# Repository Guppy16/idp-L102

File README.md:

# IDP L102
Team Name: Root g \
Robots: pi, e

The ultimate repo for the idp

## Task
Design and simulate 2 similar robots with the same controller to collect coloured blocks in an arena.

## Assumptions

Sensor Modules:
- Colour sensor: 1 pixel camera; range of 1 - 10 cm
- Ultrasound sensor: Distance sensor; range = 20 - 140 cm; 3 cm resolution; 5% std
- IR sensor: Same as ultrasound
- Position sensor: GPS sensor; 1 cm accuracy; 3cm resolution
- Rotation sensor: Compass sensor; 5cm resolution

---
## Quick Links
- [Webots Tutorials](https://cyberbotics.com/doc/guide/tutorials)
- [Parts list](https://www.vle.cam.ac.uk/pluginfile.php/19716321/mod_resource/content/0/Tools%20and%20Parts%20List%20Rev%202.0.pdf)
- [CAD Model](https://drive.google.com/drive/folders/1H2YYnImyA4o20oNFYkEqHbo80u9imQ9U?usp=sharing)
- [G Drive Folder](https://drive.google.com/drive/folders/1ipIikCvn5a5h6eHkmM2m4k-qFC2ZiWPo)

---
## Schedule
- Week 1
  - Tue 26 14:30 - [First Presentation](https://docs.google.com/presentation/d/1Jz8pw5dtujUt2GG7nFzDspJj2hsbr5QpLF5pbWbA2lo)
- Week 2
  - Thurs 28 16:00 - [First Report](https://docs.google.com/presentation/d/1Jz8pw5dtujUt2GG7nFzDspJj2hsbr5QpLF5pbWbA2lo)
  - Tue 2 14:30 - [Progress Meeting 1](https://docs.google.com/presentation/d/1rXteifI9VppYjKGW0S_Uu-YhoCQ_Fu2L5HWq04Rq7eM)
- Week 3
  - Tue 9 14:30 - [Progress Meeting 2](https://docs.google.com/presentation/d/10YraGNGObi2IVQ-5OzObUJLeiZdhKT9rYpSfk6eRZUg)
- Week 4
  - Thurs 11 09:00 - First Competition
  - Tue 16 09:00 - [Final Presentation](https://docs.google.com/presentation/d/1EIgQiFh6fY0tn3hVZZiFkF7x_DoJgEBwd8sGT5k-Sp4)
  - Wed 17 14:00 - Final Competition
- Week 5
  - Mon 22 16:00 - Final Report and Documentation Deadline

## Plan
- [Gannt Chart](https://docs.google.com/spreadsheets/d/1-Yt5QpvAf2re6IKUbvELp7eMGsR5QatMflTM9JjYLDc)

- Before the first Presenetation ~ 5 days
  - [x] Gannt chart -> [ ] Make this better
  - [x] Get used to Webots ~ 2 days
  - [x] Initial CAD and PCB design ~ 5
  - [x] Inital algorithms for navigation ~ 4
- Before progress Meeting 1 ~ 7 days
  - [x] Complete simulation of environment (2 robots)
  - [x] Complete cad design of bulk components ~ 5
  - [x] Finished full schematic ~ 3
  - [x] Started implementing algorithms ~ 3
- Before Progress Meeting 2 ~ 7 days
  - [x] Finished CAD design
  - [x] Implemented Algorithms
  - [x] Start documentation
- Before First Competition ~ 2 days
  - [x] Fully tested algorithms in simulation
- Before Final Presentation
  - [x] Complete presentation ~ 
- Before Final Competition
  - [x] Improved the simulation environment
  - [x] Improved algorithms
- Before Final Report
  - [x] Mechanics Docs
  - [x] Electrical Docs
  - [x] Software Docs
  - [x] Cleanup README file

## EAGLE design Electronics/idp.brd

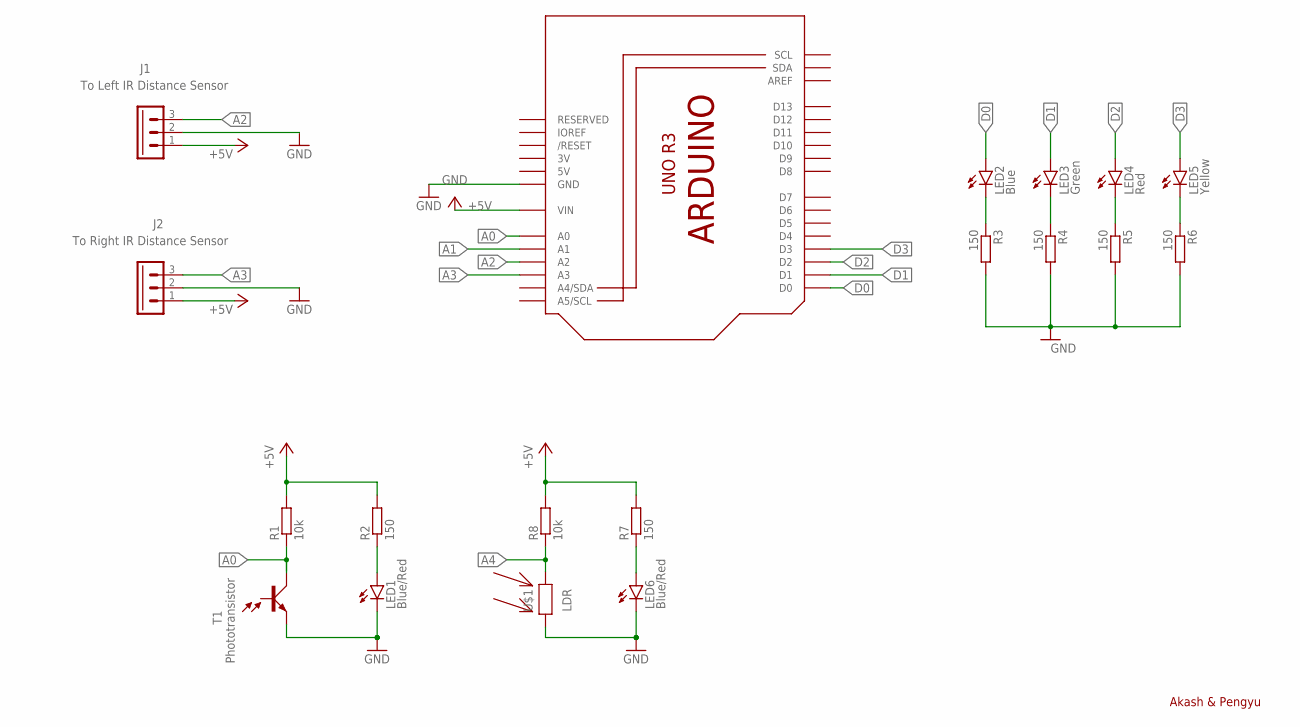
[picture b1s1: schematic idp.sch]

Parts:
J1: To Left IR Distance Sensor; 7395-03
J2: To Right IR Distance Sensor; 7395-03
LED1, LED6: Blue/Red; LED3MM
LED2: Blue; LED3MM
LED3: Green; LED3MM
LED4: Red; LED3MM
LED5: Yellow; LED3MM
M1: IDP_PROTOBOARD; IDP_PROTO
R1, R8: 10k; 0204/7
R2, R7: 150; 0204/7
R3, R4, R5, R6: 150; 0204V
T1: Phototransistor; SFH303
U$1: LDR

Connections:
3V: M1.3V
5V: M1.5V, M1.5V@0 (5V), M1.5V@1 (5V), M1.5V@2 (5V), M1.5V@3 (5V), M1.5V@4 (5V), M1.5V@5 (5V), M1.5V@6 (5V), M1.5V@7 (5V), M1.5V@8 (5V), M1.5V@9 (5V), M1.5V@10 (5V), M1.5V@11 (5V), M1.5V@12 (5V), M1.5V@13 (5V), M1.5V@14 (5V), M1.5V@15 (5V), M1.5V@16 (5V), M1.5V@17 (5V), M1.5V@18 (5V), M1.5V@19 (5V), M1.5V@20 (5V), M1.5V@21 (5V), M1.5V@22 (5V), M1.5V@23 (5V), M1.5V@24 (5V), M1.5V@25 (5V), M1.5V@26 (5V), M1.5V@27 (5V), M1.5V@28 (5V), M1.5V@29 (5V), M1.5V@30 (5V), M1.5V@31 (5V), M1.5V@32 (5V), M1.5V@33 (5V), M1.5V@34 (5V), M1.5V@35 (5V), M1.5V@36 (5V), M1.5V@37 (5V), M1.5V@38 (5V), M1.5V@39 (5V), M1.5V@40 (5V)
+5V: J1.1, J2.1, M1.VIN, R1.2, R2.2, R7.2, R8.2
A0: M1.A0, R1.1, T1.2 (C)
A1: M1.A1
A2: J1.3, M1.A2
A3: J2.3, M1.A3
A4: R8.1, U$1.P$2
D0: LED2.A, M1.D0
D1: LED3.A, M1.D1
D2: LED4.A, M1.D2
D3: LED5.A, M1.D3
GND: J1.2, J2.2, LED1.K (C), LED6.K (C), M1.GND, M1.GND16 (GND), M1.GND17 (GND), M1.GND18 (GND), M1.GND19 (GND), M1.GND20 (GND), M1.GND21 (GND), M1.GND22 (GND), M1.GND23 (GND), M1.GND24 (GND), M1.GND25 (GND), M1.GND@1 (GND), M1.GND@2 (GND), M1.GND@3 (GND), M1.GND@4 (GND), M1.GND@5 (GND), M1.GND@6 (GND), M1.GND@7 (GND), M1.GND@8 (GND), M1.GND@9 (GND), M1.GND@10 (GND), M1.GND@11 (GND), M1.GND@12 (GND), M1.GND@13 (GND), M1.GND@14 (GND), M1.GND@15 (GND), M1.GND@26 (GND), M1.GND@27 (GND), M1.GND@28 (GND), M1.GND@29 (GND), M1.GND@30 (GND), M1.GND@31 (GND), M1.GND@32 (GND), M1.GND@33 (GND), M1.GND@34 (GND), M1.GND@35 (GND), M1.GND@36 (GND), M1.GND@37 (GND), M1.GND@38 (GND), M1.GND@39 (GND), M1.GND@40 (GND), M1.GND@41 (GND), M1.GND@42 (GND), M1.GND@43 (GND), M1.GND@44 (GND), M1.GND@45 (GND), M1.GND@46 (GND), M1.GND@47 (GND), M1.GND@48 (GND), R3.2, R4.2, R5.2, R6.2, T1.1 (E), U$1.P$1
unnamed: LED2.K (C), R3.1
unnamed: LED6.A, R7.1
unnamed: LED1.A, R2.1
unnamed: LED3.K (C), R4.1
unnamed: LED4.K (C), R5.1
unnamed: LED5.K (C), R6.1

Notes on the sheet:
Akash & Pengyu

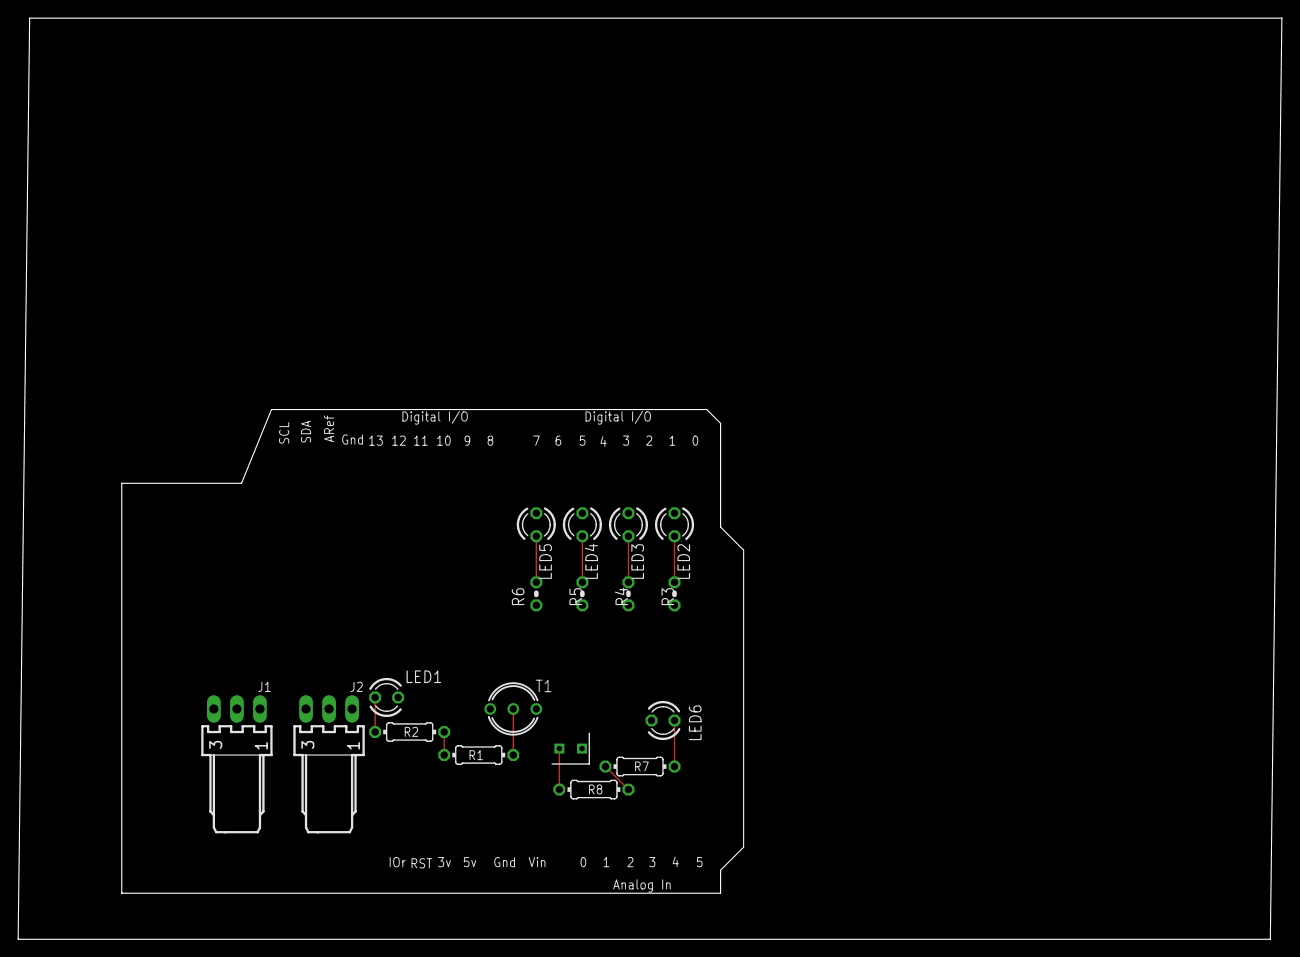
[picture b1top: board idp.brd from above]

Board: 2 copper layers, 139.4 x 101.6 mm, 19 parts (0 on the bottom side), 17 nets.

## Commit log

2021-01-21 Add files via upload
    Gantt chart generator.
2021-01-21 Added links to README
2021-01-21 Return.
2021-01-21 Added tasks and updated schedule
2021-01-21 Added idp-event.ics
2021-01-21 Updated gant chart.
2021-01-21 Added folder.
2021-01-22 Changed bars to gray.
2021-01-25 Added Arena sim in Webots/
2021-01-25 Added .idea to .gitignore.
2021-01-25 Updated gitignore for webots
2021-01-25 Remove .idea folder.
2021-01-25 Remove .DS_Store.
2021-01-27 Add my_controller and red_controller.
2021-01-28 Added blue_controller and red_controller. Robots move around with WASD and arrow keys respectively.
2021-01-28 Modified world
2021-01-30 Added schematics
2021-01-30 updated readme. added gannt chart
2021-02-01 First attempt at new robot
2021-02-01 Added First Report
2021-02-01 With distance sensor
2021-02-01 Rename idp2.brd to idp.brd
2021-02-01 Rename idp2.sch to idp.sch
2021-02-02 Proto added
2021-02-02 Updated eagle schematics
2021-02-02 Added proto file
2021-02-04 cleaned up the readme (typos, updated completed tasks)
2021-02-04 Renamed robot
2021-02-04 new proto file
2021-02-04 added *dysfunctional* gps controller
2021-02-04 actually added *dysfunctional* gps controller
2021-02-04 Corrected IS modifiers in proto file
2021-02-04 added compass to robotical robot bot
2021-02-04 Schematics change
2021-02-04 added complete first draft return home controller
2021-02-04 changed controller name and debugged controller
2021-02-04 Renamed files
2021-02-05 changed wall colour in wbt world
2021-02-05 started script to convert robot to proto
2021-02-05 world contains only root-g robots
2021-02-05 removed outdated gps controller
2021-02-05 fixed bearing issues with gp controller
2021-02-05 Finished controller to return robotical robo robot bot home
2021-02-05 commented out print values which he used for tests
2021-02-05 cleaned up world for testing
2021-02-05 cleaned up go_home controller
2021-02-05 cleaned up wbts and protos
2021-02-05 added main controller
2021-02-05 updated controllers
2021-02-06 added camera and changed dimensions of wbts robot
2021-02-06 Added rotating servo motor with distance sensor
2021-02-06 fixed rotation axis of servo motor
2021-02-06 Changed anchor for wheels
2021-02-07 updated schematics
2021-02-07 led indicators added
2021-02-08 Schematics changed
2021-02-08 PCB board
2021-02-09 added LDR. created board
2021-02-09 checked for divide by zero warning
2021-02-09 control robot to reverse out of home
2021-02-09 north aligned with +ve x-axis.
2021-02-09 modified heading code
2021-02-09 Chagned a buch of stuff.
2021-02-09 Some more random stuff.
2021-02-09 modified exit_home
2021-02-09 shifted ds sensor down
2021-02-09 implemented robocar class
2021-02-09 modified robocar. added camera controller
2021-02-09 modified main_controller
2021-02-09 modified robot_to_proto
2021-02-09 go_home implemented
2021-02-09 modified robocar
2021-02-09 robocar modified
2021-02-09 modified protos and robocar controller
2021-02-09 began work on searching for blocks including go_to_middle
2021-02-09 implemented stack
2021-02-10 updated protos
2021-02-10 colour detection
2021-02-10 continued working on finding blocks algo
2021-02-10 added file handling func. store blocks, other robo
2021-02-10 testing find_blocks
2021-02-11 got find_blocks() fully working
2021-02-11 tested and corrected utils functions
2021-02-11 rotates until reached north
2021-02-11 created task manager
2021-02-11 finished untested get_blocks()
2021-02-11 added comments
2021-02-11 Added debugging statements.
2021-02-11 implemented task manager, file handling
2021-02-11 commented out print statements
2021-02-11 Moved functions out of robocar into main.
2021-02-11 changed tasks
2021-02-11 Updated changes.
2021-02-11 changed block rotation
2021-02-11 both robots move
2021-02-11 Tried and failed to trouleshoot the color sensing.
2021-02-11 saved webots file
2021-02-11 goes to block
2021-02-11 changed stuff
2021-02-11 stopper other robot. random block picked up
2021-02-13 Code before 1st test round
2021-02-15 added leds to webots robot and removed servo motor
2021-02-15 Latest changes.
2021-02-16 modified block class
2021-02-16 added helper functions for sorting and pos values in utils
2021-02-16 finds block, detects colour, and delivers it home
2021-02-16 Ignore blocks close to home. Go to middle if no more block found
2021-02-16 Tried resetting the list of blocks
2021-02-16 move one robot at a time
2021-02-16 added function to rotate robot through certain number of degrees
2021-02-16 worked a bit on drive_around_block()
2021-02-16 increase range of block search
2021-02-16 fixed merge errrors
2021-02-16 World file with super easy blocks.
2021-02-16 resetting target block if it finds the same one
2021-02-16 finished first draft of drive_around_block()
2021-02-16 blue robot should work
2021-02-17 almost fixed turning error. also fixed other bugs
2021-02-17 replaced turn_to with rotate_to_location
2021-02-17 changed tolerances
2021-02-17 finished and implemented drive_around_block()
2021-02-17 implemented drive_around_block a bit more
2021-02-17 made the json not be weird
2021-02-17 just a neat little commit to make your friends smile
2021-02-17 fixed rotate_to_location
2021-02-17 testing new scenario
2021-02-17 removed print statements. Don't store blocks in a file. updated list of colours
2021-02-17 got everything to seem to be working well
2021-02-17 check for unkown colours
2021-02-17 improved code
2021-02-17 improved collision and colour detection
2021-02-17 shouldn't crash into a wall
2021-02-17 return_home function jic of a crash
2021-02-17 cleaned up print statements
2021-02-17 bottom distance sensor limitted to 1.4 m
2021-02-17 updated proto
2021-02-17 reduced range of ds sensors
2021-02-17 print block colour in colorama
2021-02-17 made some changes to the block detection and sensor noise
2021-02-17 removed files and reordered block search mechanism
2021-02-17 final competition
2021-02-20 final competition repo
2021-02-20 Removed redundant folders. Modified Readme
2021-02-20 removed old proto
2021-02-20 modified readme
2021-02-21 Mech docs
2021-02-22 updated readme with assumptions
2021-02-22 cleaned up code. updated readme. added docs
